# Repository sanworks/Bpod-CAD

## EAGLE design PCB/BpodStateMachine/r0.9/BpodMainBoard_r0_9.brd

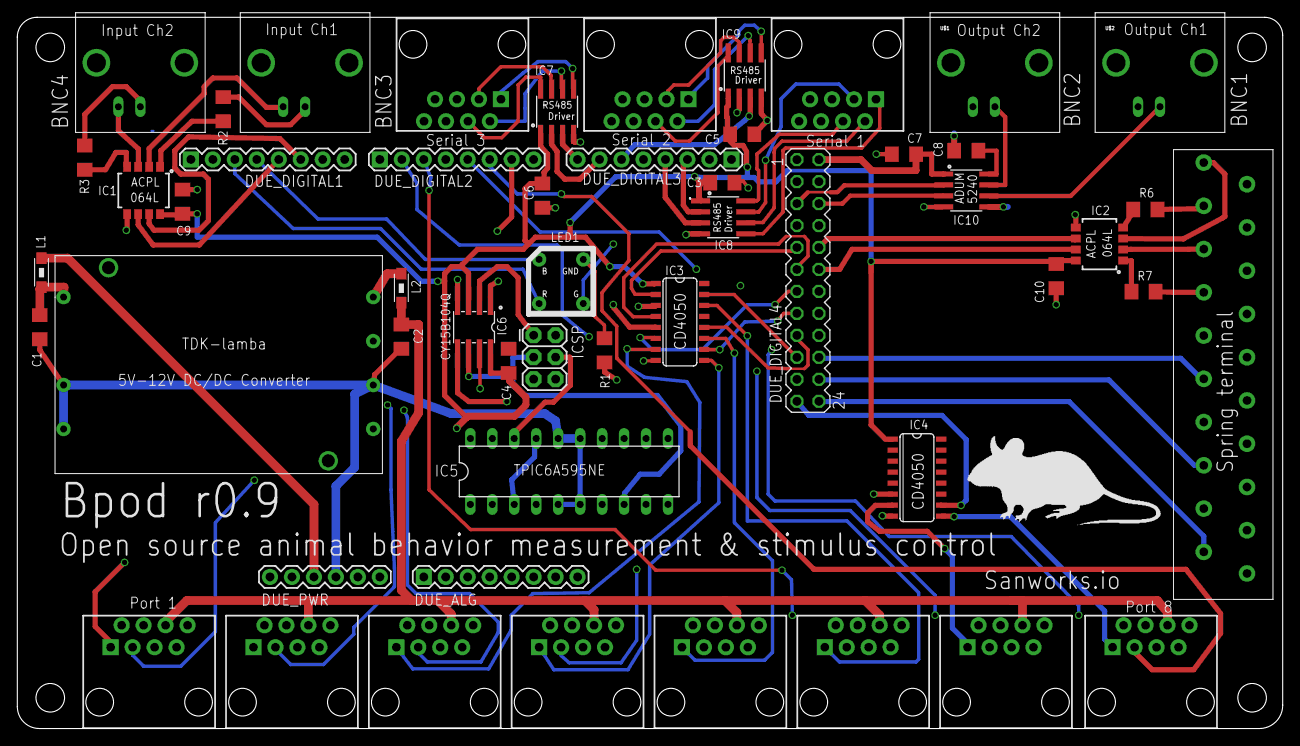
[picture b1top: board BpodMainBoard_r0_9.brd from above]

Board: 4 copper layers, 146.3 x 82.2 mm, 57 parts (0 on the bottom side), 93 nets.

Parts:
C1, C2: 22uf; 1206
C3, C4, C5, C6, C7, C8, C9, C10: 0.1uf; 1206
DUE_ALG: 1X08
DUE_DIGITAL1, DUE_DIGITAL2, DUE_DIGITAL3: 1X08
DUE_DIGITAL4: MA12-2
DUE_PWR: 1X06
IC1, IC2: OPTOISOLATOR-2SOIC8; SO08-2
IC3, IC4: CD4050; SO16
IC5: DIL20
IC6: CY15B104Q-SXI; SO08-UNIVERSAL
IC7, IC8, IC9: SN65HVD31DR; SO08
IC10: ADUM5240; SO08
ICSP: AVR_SPI_PRG_6PTH; 2X3
JP1, JP2, JP3, JP4: STAND-OFF
L1, L2: 1206
PORT1, PORT2, PORT3, PORT4, PORT5, PORT6, PORT7, PORT8: RJ45-8PTH; RJ45-8
R1: 47; 1206
R2, R3, R6, R7: 1k; 1206
SERIAL1, SERIAL2: RJ45-8PTH; RJ45-8
SYNC: RJ45-8PTH; RJ45-8
U$1, U$2, U$3, U$4: BNCPTH; BNC
U$5: TDK_LAMBDA_5V_TO_12V; TDK_LAMBDA_5V_12V
U$6: 10POS_SPRING_TERMINAL; 10POS_SCREW_TERMINAL
U$7: MOUSELOGO
U$8: SQUARE_TRICOLOR_LED

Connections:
5V: DUE_PWR.3, IC5.3, IC5.17, L1.2, PORT1.4, PORT2.4, PORT3.4, PORT4.4, PORT5.4, PORT6.4, PORT7.4, PORT8.4
12V: C2.1, L2.1, PORT1.6, PORT2.6, PORT3.6, PORT4.6, PORT5.6, PORT6.6, PORT7.6, PORT8.6
BNCIN1: DUE_DIGITAL1.6, IC1.7
BNCIN2: DUE_DIGITAL1.5, IC1.6
BNC_OUT1: DUE_DIGITAL4.6, IC10.3
BNC_OUT2: DUE_DIGITAL4.5, IC10.2
FRAM_CS: DUE_DIGITAL2.7, IC6.1
FRAM_HLD: DUE_ALG.4, IC6.7
GND: C3.2, C5.2, C6.2, C7.2, C9.2, C10.1, DUE_PWR.5, IC1.5, IC2.5, IC3.8, IC4.8, IC5.4, IC5.14, IC6.4, IC7.4, IC8.4, IC9.4, IC10.4, PORT1.5, PORT2.5, PORT3.5, PORT4.5, PORT5.5, PORT6.5, PORT7.5, PORT8.5, R1.1, U$6.P$12, U$6.P$14, U$6.P$16
ISOGND: C8.2, IC10.5, U$1.GND, U$2.GND
LED_BLUE: DUE_DIGITAL1.4, U$8.P$3
LED_GREEN: DUE_DIGITAL4.14, U$8.P$1
LED_RED: DUE_DIGITAL1.3, U$8.P$4
MOSI: IC5.18, IC6.5, ICSP.4
unnamed: R3.2, U$4.S
unnamed: R2.2, U$3.S
unnamed: IC1.3, U$4.GND
unnamed: IC1.2, U$3.GND
unnamed: R6.2, U$6.P$19
unnamed: IC10.6, U$2.S
unnamed: IC10.7, U$1.S
unnamed: IC5.19, PORT1.7
unnamed: IC5.20, PORT2.7
unnamed: IC5.1, PORT3.7
unnamed: IC5.2, PORT4.7
unnamed: IC5.9, PORT5.7
unnamed: IC5.10, PORT6.7
unnamed: IC5.11, PORT7.7
unnamed: IC5.12, PORT8.7
unnamed: IC7.8, SYNC.4
unnamed: IC7.7, SYNC.3
unnamed: IC7.6, SYNC.2
unnamed: IC7.5, SYNC.1
unnamed: DUE_DIGITAL3.7, IC7.2
unnamed: IC2.4, R6.1
unnamed: IC2.1, R7.1
unnamed: R1.2, U$8.P$2
unnamed: C8.1, IC10.8
unnamed: DUE_DIGITAL3.8, IC7.3
unnamed: IC8.8, SERIAL1.4
unnamed: IC8.7, SERIAL1.3
unnamed: IC8.6, SERIAL1.2
unnamed: IC8.5, SERIAL1.1
unnamed: IC9.8, SERIAL2.4
unnamed: IC9.7, SERIAL2.3
unnamed: IC9.6, SERIAL2.2
unnamed: IC9.5, SERIAL2.1
unnamed: DUE_DIGITAL3.3, IC8.2
unnamed: IC2.3, U$6.P$20
unnamed: R7.2, U$6.P$17
unnamed: IC2.2, U$6.P$18
unnamed: C1.1, L1.1, U$5.5VIN
unnamed: L2.2, U$5.12VOUT
unnamed: DUE_DIGITAL3.4, IC8.3
unnamed: DUE_DIGITAL3.5, IC9.2
unnamed: DUE_DIGITAL3.6, IC9.3
unnamed: IC1.1, R2.1
unnamed: IC1.4, R3.1
PGND: C1.2, C2.2, DUE_PWR.4, IC5.5, IC5.6, IC5.15, IC5.16, U$5.5VGND, U$5.12VGND, U$5.PWR
PORT1INPUT: IC3.3, PORT1.1
PORT1IN_3V3: DUE_DIGITAL4.9, IC3.2
PORT1LED: DUE_DIGITAL1.7, PORT1.3
PORT2INPUT: IC3.5, PORT2.1
PORT2IN_3V3: DUE_DIGITAL4.11, IC3.4
PORT2LED: DUE_DIGITAL1.8, PORT2.3
PORT3INPUT: IC3.7, PORT3.1
PORT3IN_3V3: DUE_DIGITAL4.13, IC3.6
PORT3LED: DUE_DIGITAL2.1, PORT3.3
PORT4INPUT: IC3.9, PORT4.1
PORT4IN_3V3: DUE_DIGITAL4.15, IC3.10
PORT4LED: DUE_DIGITAL2.2, PORT4.3
PORT5INPUT: IC3.11, PORT5.1
PORT5IN_3V3: DUE_DIGITAL4.17, IC3.12
PORT5LED: DUE_DIGITAL2.3, PORT5.3
PORT6INPUT: IC3.14, PORT6.1
PORT6IN_3V3: DUE_DIGITAL4.19, IC3.15
PORT6LED: DUE_DIGITAL2.4, PORT6.3
PORT7INPUT: IC4.7, PORT7.1
PORT7IN_3V3: DUE_DIGITAL4.21, IC4.6
PORT7LED: DUE_DIGITAL2.5, PORT7.3
PORT8INPUT: IC4.9, PORT8.1
PORT8IN_3V3: DUE_DIGITAL4.23, IC4.10
PORT8LED: DUE_DIGITAL2.6, PORT8.3
RCK: DUE_DIGITAL4.3, IC5.7
SPI_CLK: IC5.8, IC6.6, ICSP.3
SPI_MISO: IC6.2, ICSP.1
UPPER_5V: C7.1, DUE_DIGITAL4.2, IC10.1
VCC: C3.1, C4.2, C5.1, C6.1, C9.1, C10.2, DUE_PWR.2, IC1.8, IC2.8, IC3.1, IC4.1, IC6.3, IC6.8, IC7.1, IC8.1, IC9.1
WIREOUT3: DUE_DIGITAL4.20, U$6.P$15
WIRE_INPUT1: DUE_DIGITAL4.12, IC2.7
WIRE_INPUT2: DUE_DIGITAL4.10, IC2.6
WIRE_OUT1: DUE_DIGITAL4.24, U$6.P$11
WIRE_OUT2: DUE_DIGITAL4.22, U$6.P$13

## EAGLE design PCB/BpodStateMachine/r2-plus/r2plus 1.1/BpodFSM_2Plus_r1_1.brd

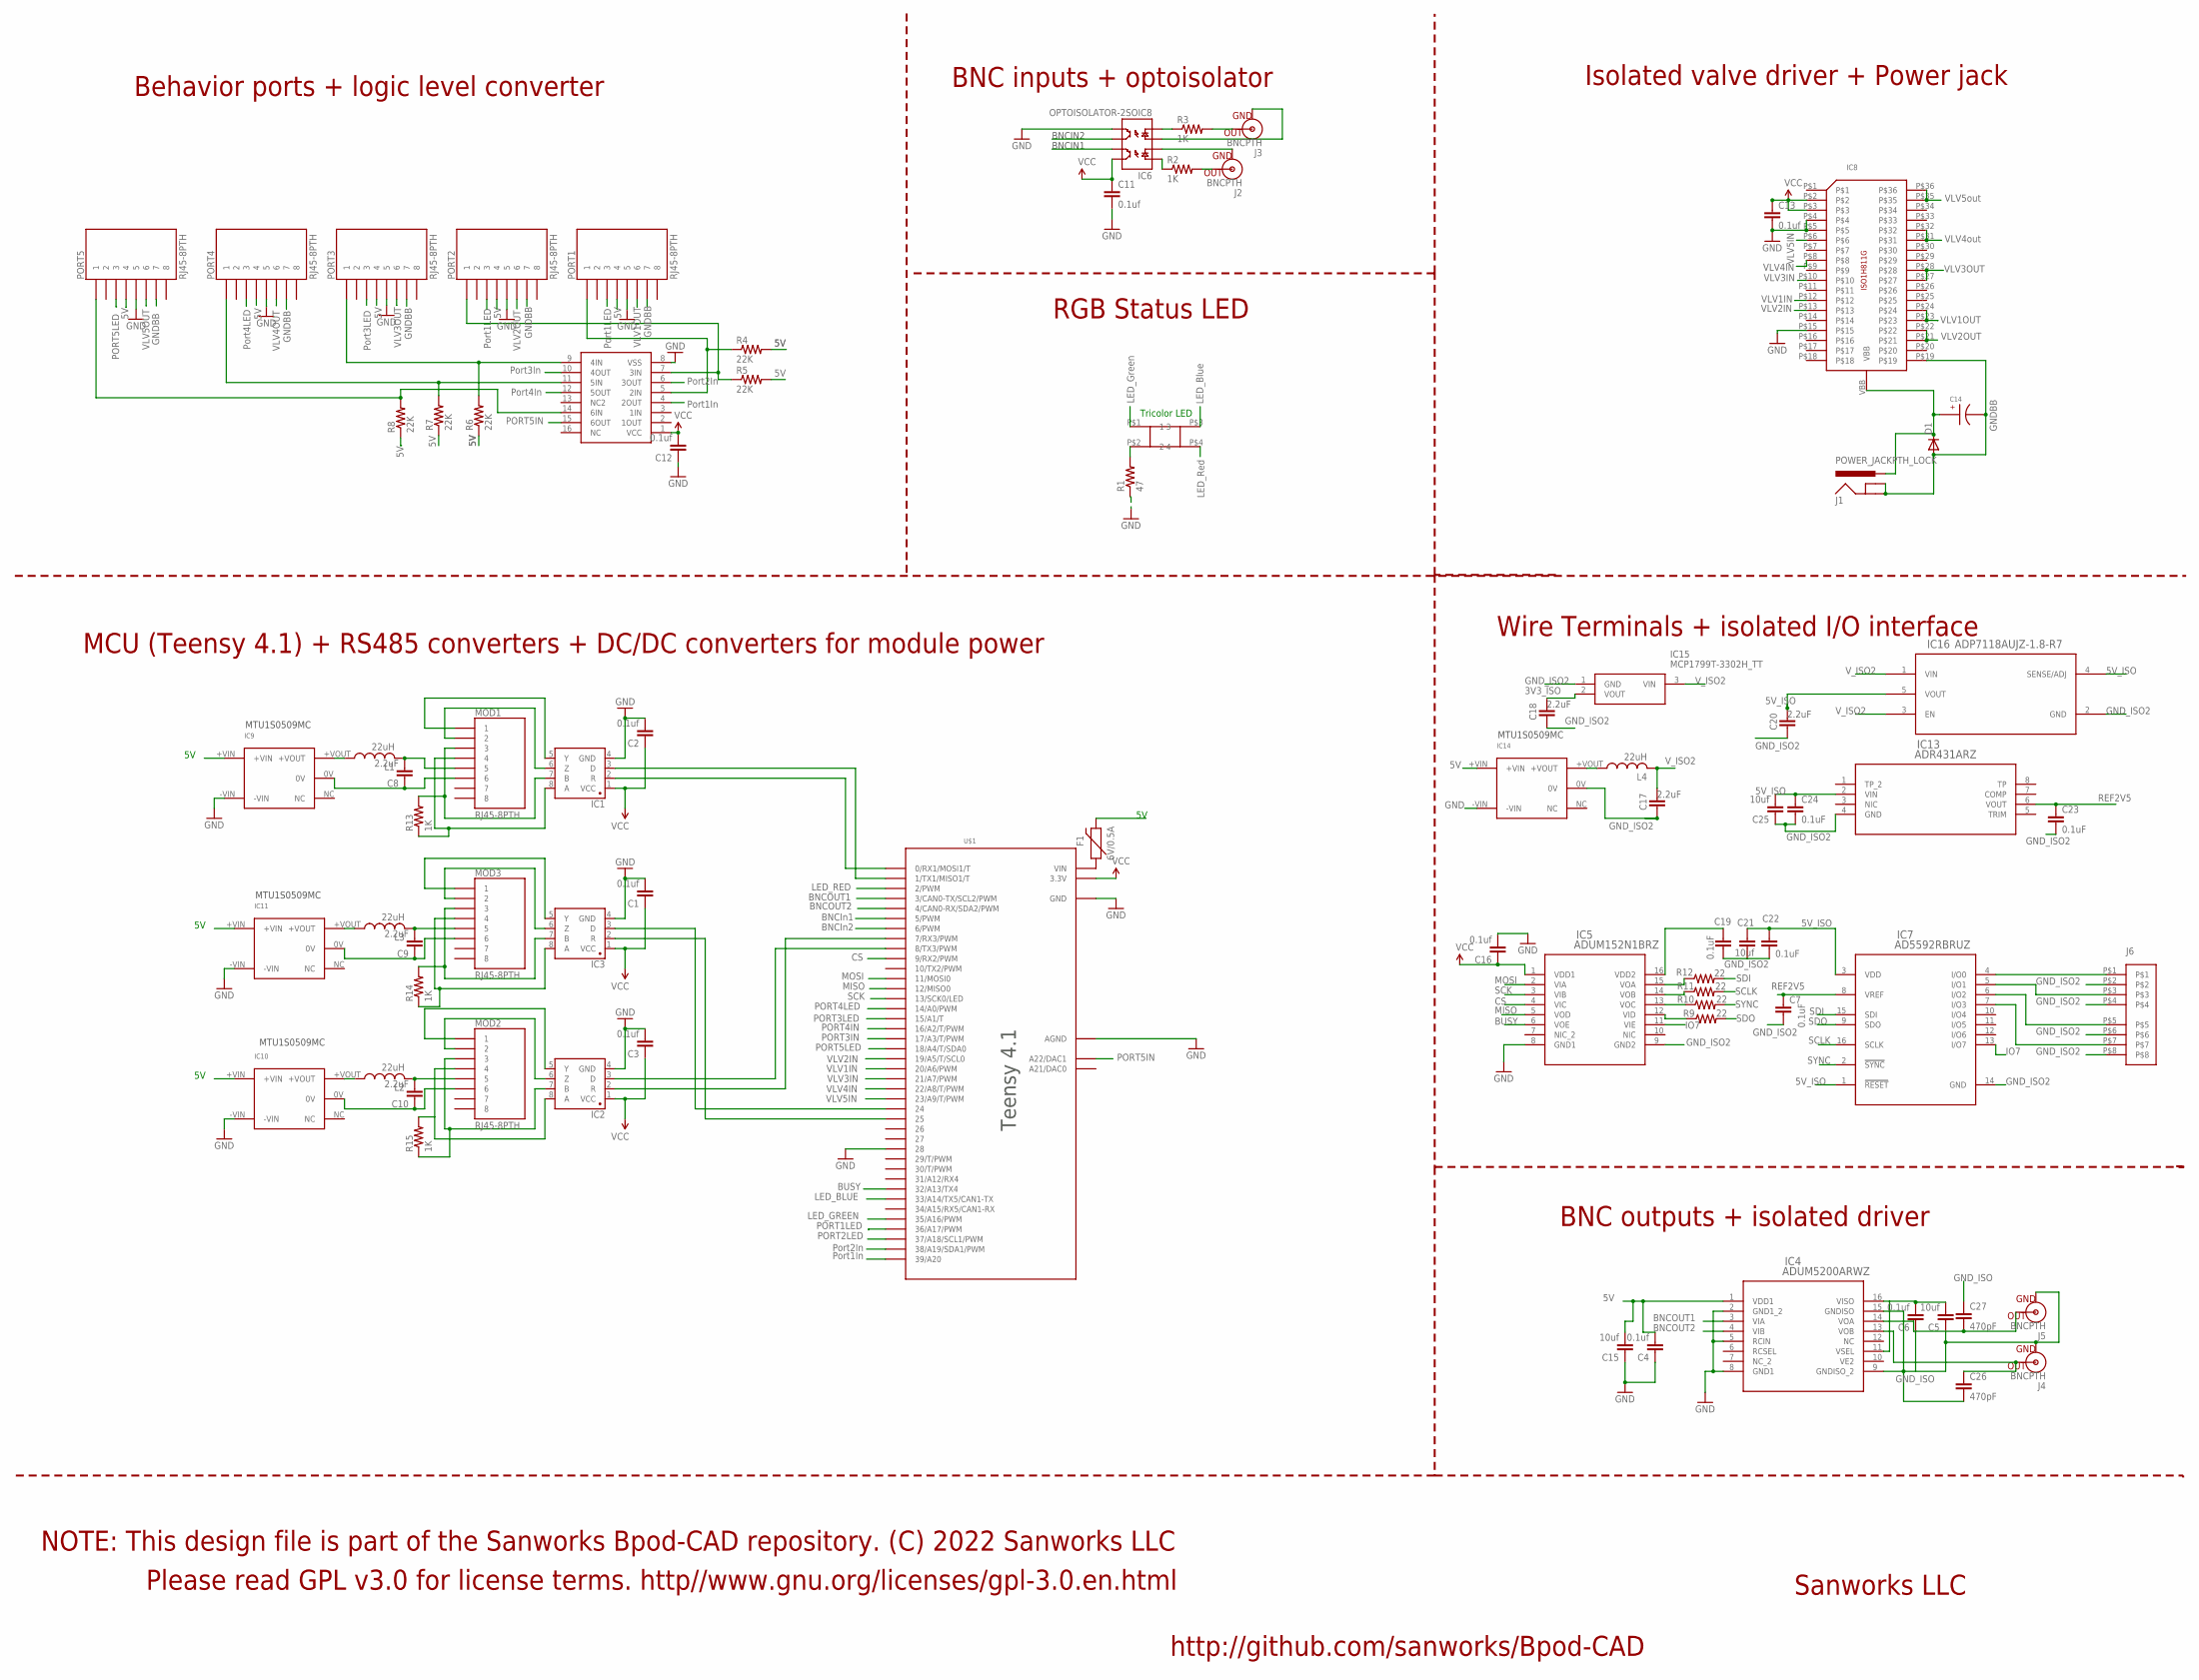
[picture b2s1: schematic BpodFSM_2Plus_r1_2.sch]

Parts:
C1, C2, C3, C4, C6, C11, C12, C13, C16: 0.1uf; 0805
C5, C15, C21, C25: 10uf; 1206@1
C7, C19, C22, C23, C24: 0.1uF; 0805
C8, C9, C10, C17, C18, C20: 2.2uF; 0805
C14: EEE-FK1H100UR
C26, C27: 470pF; 0805
D1: DIODE-DO214AA; DO214AA
F1: 6V/0.5A; 1206
IC1, IC2, IC3: SN65HVD31DR; SO08
IC4: ADUM5200ARWZ; RW_16
IC5: ADUM152N1BRZ; R-16_ADI
IC6: OPTOISOLATOR-2SOIC8; SO08-2
IC7: AD5592RBRUZ; RU_16_ADI
IC8: ISO1H811G
IC9, IC10, IC11: 9V; MTU1D0505MC
IC12: CD4050; SO16
IC13: ADR431ARZ; R_8_ADI
IC14: 5V; MTU1D0505MC
IC15: MCP1799T-3302H_TT; SOT95P237X112-3N
IC16: ADP7118AUJZ-1.8-R7; UJ_5
J1: POWER_JACKPTH_LOCK; POWER_JACK_PTH_LOCK
J2, J3, J4, J5: BNCPTH; BNC
J6: 8POS_MOLEX_SOCKET
L1, L2, L3, L4: 22uH; L3225M
MOD1, MOD2, MOD3: RJ45-8PTH; RJ45-8
PORT1, PORT2, PORT3, PORT4, PORT5: RJ45-8PTH; RJ45-8
R1: 47; 1206
R2, R3, R13, R14, R15: 1K; 1206
R4, R5, R6, R7, R8: 22K; 1206
R9, R10, R11, R12: 22; R0805
U$1: TEENSY_3.6_DIL
U$8: SQUARE_TRICOLOR_LED

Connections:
5V: C4.2, C15.2, F1.2, IC4.1 (VDD1), IC9.+VIN, IC10.+VIN, IC11.+VIN, IC14.+VIN, PORT1.4, PORT2.4, PORT3.4, PORT4.4, PORT5.4, R4.2, R5.2, R6.1, R7.1, R8.1
BNCIN1: IC6.7 (EM1), U$1.6 (6/PWM)
BNCIN2: IC6.6 (CL2), U$1.5 (5/PWM)
BNCOUT1: IC4.3 (VIA), U$1.3 (3/CAN0-TX/SCL2/PWM)
BNCOUT2: IC4.4 (VIB), U$1.4 (4/CAN0-RX/SDA2/PWM)
BUSY: IC5.6 (VOE), U$1.32/A13 (32/A13/TX4)
CS: IC5.4 (VIC), U$1.9 (9/RX2/PWM)
GND: C1.2, C2.2, C3.2, C4.1, C11.2, C12.1, C13.2, C15.1, C16.2, IC1.4 (GND), IC2.4 (GND), IC3.4 (GND), IC4.2 (GND1_2), IC4.5 (RCIN), IC4.8 (GND1), IC5.8 (GND1), IC6.5 (EM2), IC8.P$4, IC8.P$5, IC8.P$15, IC9.-VIN, IC10.-VIN, IC11.-VIN, IC12.8 (VSS), IC14.-VIN, PORT1.5, PORT2.5, PORT3.5, PORT4.5, PORT5.5, R1.1, U$1.28, U$1.AGND, U$1.GND, U$1.GND1 (GND); also elsewhere on the board
GNDBB: C14.CATHODE, D1.A, IC8.P$19, J1.GND, J1.GNDBREAK, PORT1.7, PORT2.7, PORT3.7, PORT4.7, PORT5.7
GND_ISO: C5.1, C6.1, C26.2, C27.1, IC4.9 (GNDISO_2), IC4.15 (GNDISO), J4.GND, J5.GND
IO7: IC5.11 (VIE), IC7.13 (I/O7)
LED_BLUE: U$1.33/A14 (33/A14/TX5/CAN1-TX), U$8.P$3 (3)
LED_GREEN: U$1.35/A16 (35/A16/PWM), U$8.P$1 (1)
LED_RED: U$1.2 (2/PWM), U$8.P$4 (4)
MISO: IC5.5 (VOD), U$1.12 (12/MISO0)
MOSI: IC5.2 (VIA), U$1.11 (11/MOSI0)
unnamed: IC3.8 (A), MOD3.4, R14.1
unnamed: IC3.7 (B), MOD3.3, R14.2
unnamed: IC3.6 (Z), MOD3.2
unnamed: IC3.5 (Y), MOD3.1
unnamed: IC3.2 (R), U$1.25
unnamed: IC3.3 (D), U$1.24
unnamed: IC1.8 (A), MOD1.4, R13.1
unnamed: IC1.7 (B), MOD1.3, R13.2
unnamed: IC1.6 (Z), MOD1.2
unnamed: IC1.5 (Y), MOD1.1
unnamed: IC1.2 (R), U$1.0 (0/RX1/MOSI1/T)
unnamed: IC1.3 (D), U$1.1 (1/TX1/MISO1/T)
unnamed: IC6.3 (A2), J3.GND
unnamed: J3.S (OUT), R3.2
unnamed: J2.S (OUT), R2.2
unnamed: IC6.2 (C1), J2.GND
unnamed: IC2.8 (A), MOD2.4, R15.2
unnamed: IC2.7 (B), MOD2.3, R15.1
unnamed: IC2.6 (Z), MOD2.2
unnamed: IC12.7 (3IN), PORT2.1, R5.1
unnamed: IC2.5 (Y), MOD2.1
unnamed: IC2.2 (R), U$1.7 (7/RX3/PWM)
unnamed: C8.2, L1.2, MOD1.5
unnamed: IC12.9 (4IN), PORT3.1, R6.2
unnamed: R1.2, U$8.P$2 (2)
unnamed: C8.1, IC9.0V, MOD1.6
unnamed: C5.2, C6.2, IC4.11 (VSEL), IC4.16 (VISO)
unnamed: IC2.3 (D), U$1.8 (8/TX3/PWM)
unnamed: F1.1, U$1.VIN
unnamed: IC7.4 (I/O0), J6.P$1
unnamed: IC12.11 (5IN), PORT4.1, R7.2
unnamed: C27.2, IC4.14 (VOA), J5.S (OUT)
unnamed: C26.1, IC4.13 (VOB), J4.S (OUT)
unnamed: IC7.5 (I/O1), J6.P$3
unnamed: IC7.6 (I/O2), J6.P$5
unnamed: IC7.7 (I/O3), J6.P$7
unnamed: IC14.+VOUT, L4.1
unnamed: IC5.15 (VOA), R12.1
unnamed: IC9.+VOUT, L1.1
unnamed: IC5.14 (VOB), R11.1
unnamed: IC12.14 (6IN), PORT5.1, R8.2
unnamed: IC5.13 (VOC), R10.1
unnamed: C10.1, IC10.0V, MOD2.6
unnamed: C10.2, L2.2, MOD2.5
unnamed: IC10.+VOUT, L2.1
unnamed: IC5.12 (VID), R9.1
unnamed: C9.1, IC11.0V, MOD3.6
unnamed: C9.2, L3.2, MOD3.5
unnamed: IC11.+VOUT, L3.1
unnamed: IC6.1 (A1), R2.1
unnamed: IC6.4 (C2), R3.1
unnamed: IC12.5 (2IN), PORT1.1, R4.1
PORT1IN: IC12.4 (2OUT), U$1.39/A20
PORT1LED: PORT1.3, U$1.36/A17 (36/A17/PWM)
PORT2IN: IC12.6 (3OUT), U$1.38/A19 (38/A19/SDA1/PWM)
PORT2LED: PORT2.3, U$1.37/A18 (37/A18/SCL1/PWM)
PORT3IN: IC12.10 (4OUT), U$1.17/A3 (17/A3/T/PWM)
PORT3LED: PORT3.3, U$1.15/A1 (15/A1/T)
PORT4IN: IC12.12 (5OUT), U$1.16/A2 (16/A2/T/PWM)
PORT4LED: PORT4.3, U$1.14/A0 (14/A0/PWM)
PORT5IN: IC12.15 (6OUT), U$1.A22 (A22/DAC1)
PORT5LED: PORT5.3, U$1.18/A4 (18/A4/T/SDA0)
REF2V5: C7.1, C23.1, IC7.8 (VREF), IC13.6 (VOUT)
SCK: IC5.3 (VIB), U$1.13 (13/SCK0/LED)
SCLK: IC7.16 (SCLK), R11.2
SDI: IC7.15 (SDI), R12.2
SDO: IC7.9 (SDO), R9.2
SYNC: IC7.2 (!SYNC), R10.2
VBB: C14.ANODE, D1.C, IC8.VBB, J1.PWR
VCC: C1.1, C2.1, C3.1, C11.1, C12.2, C13.1, C16.1, IC1.1 (VCC), IC2.1 (VCC), IC3.1 (VCC), IC5.1 (VDD1), IC6.8 (CL1), IC8.P$2, IC8.P$3, IC12.1 (VCC), U$1.3.3V, U$1.3.3V3 (3.3V)
VLV1IN: IC8.P$12, U$1.20/A6 (20/A6/PWM)
VLV1OUT: IC8.P$23, IC8.P$24, PORT1.6
VLV2IN: IC8.P$13, U$1.19/A5 (19/A5/T/SCL0)
VLV2OUT: IC8.P$21, IC8.P$22, PORT2.6
VLV3IN: IC8.P$10, U$1.21/A7 (21/A7/PWM)
VLV3OUT: IC8.P$27, IC8.P$28, PORT3.6
VLV4IN: IC8.P$8, U$1.22/A8 (22/A8/T/PWM)
VLV4OUT: IC8.P$31, IC8.P$32, PORT4.6
VLV5IN: IC8.P$6, U$1.23/A9 (23/A9/T/PWM)
VLV5OUT: IC8.P$35, IC8.P$36, PORT5.6

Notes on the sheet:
Tricolor LED
LED_Blue
LED_Red
LED_Green
BNCIN1
BNCIN2
BNCIn1
BNCIn2
Port1In
Port2In
Port3In
Port4In
Port1LED
Port3LED
Port4LED
GNDBB
VLV5out
VLV4out
Sanworks LLC
http://github.com/sanworks/Bpod-CAD
Please read GPL v3.0 for license terms. http//www.gnu.org/licenses/gpl-3.0.en.html
NOTE: This design file is part of the Sanworks Bpod-CAD repository. (C) 2022 Sanworks LLC
Behavior ports + logic level converter
BNC inputs + optoisolator
Isolated valve driver + Power jack
RGB Status LED
BNC outputs + isolated driver
MCU (Teensy 4.1) + RS485 converters + DC/DC converters for module power
Wire Terminals + isolated I/O interface
MTU1S0509MC
Teensy 4.1

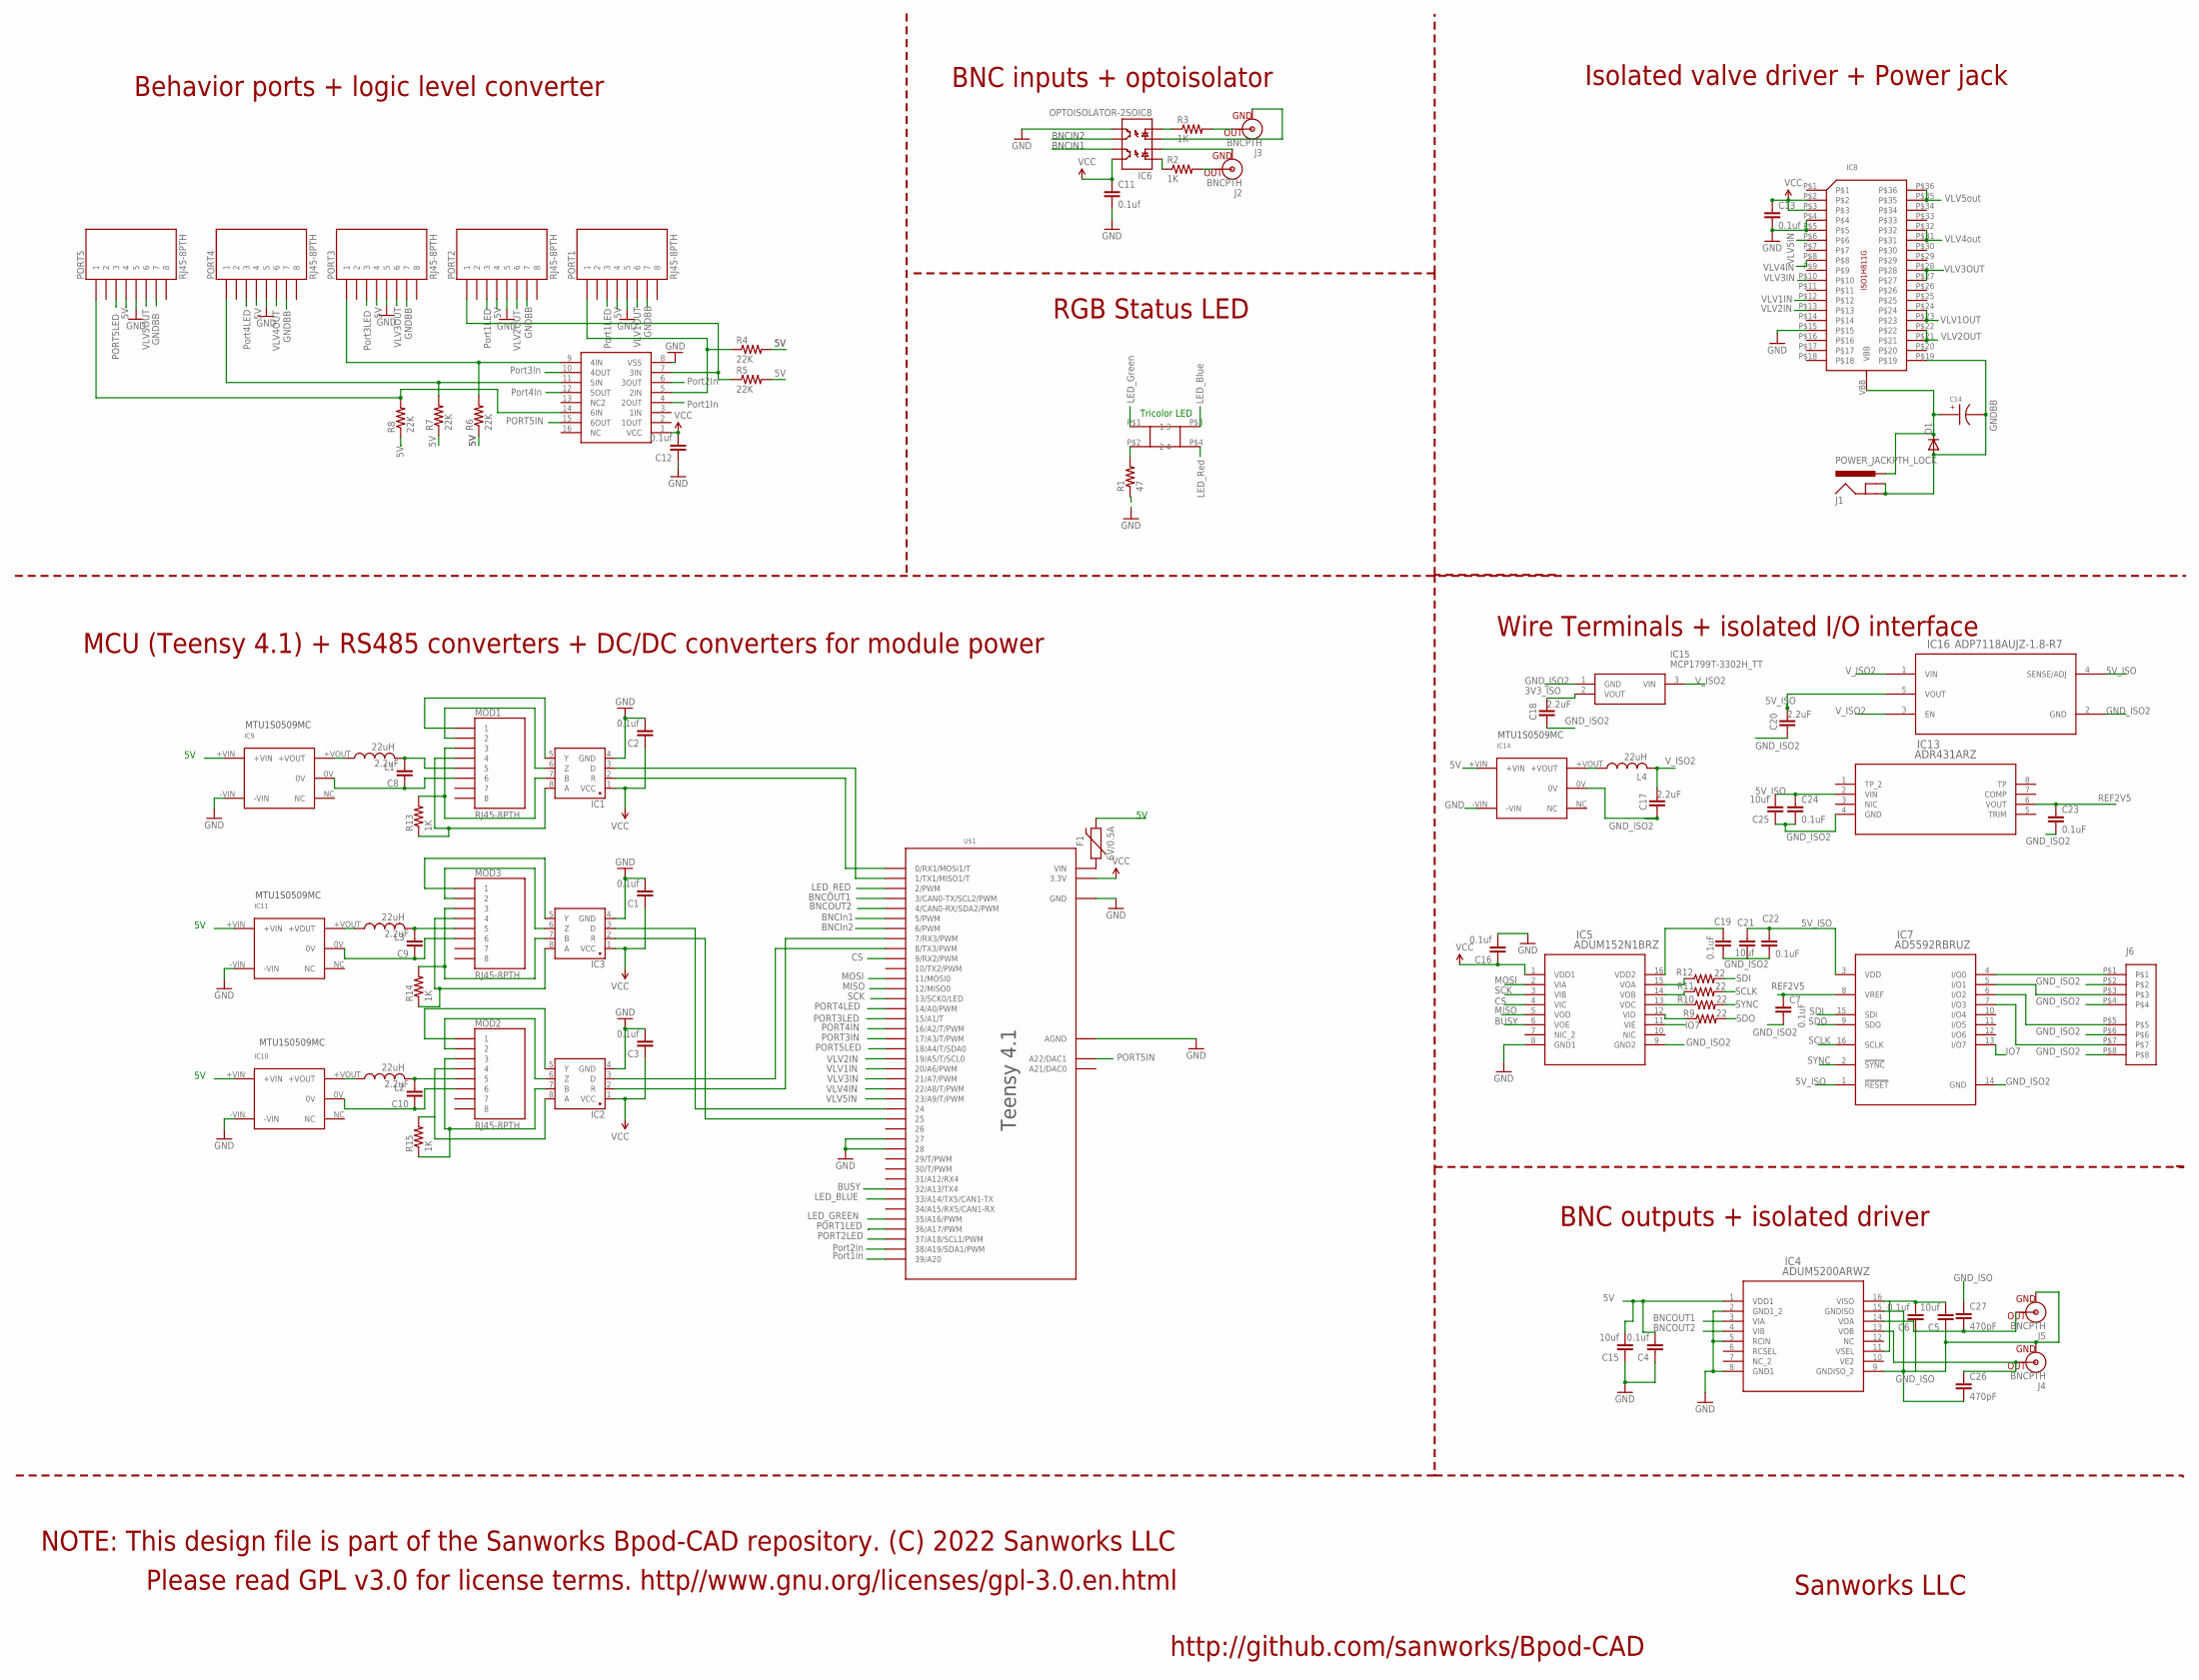
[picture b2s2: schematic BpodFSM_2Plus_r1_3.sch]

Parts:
C1, C2, C3, C4, C6, C11, C12, C13, C16: 0.1uf; 0805
C5, C15, C21, C25: 10uf; 1206@1
C7, C19, C22, C23, C24: 0.1uF; 0805
C8, C9, C10, C17, C18, C20: 2.2uF; 0805
C14: EEE-FK1H100UR
C26, C27: 470pF; 0805
D1: DIODE-DO214AA; DO214AA
F1: 6V/0.5A; 1206
IC1, IC2, IC3: SN65HVD31DR; SO08
IC4: ADUM5200ARWZ; RW_16
IC5: ADUM152N1BRZ; R-16_ADI
IC6: OPTOISOLATOR-2SOIC8; SO08-2
IC7: AD5592RBRUZ; RU_16_ADI
IC8: ISO1H811G
IC9, IC10, IC11: 9V; MTU1D0505MC
IC12: CD4050; SO16
IC13: ADR431ARZ; R_8_ADI
IC14: 5V; MTU1D0505MC
IC15: MCP1799T-3302H_TT; SOT95P237X112-3N
IC16: ADP7118AUJZ-1.8-R7; UJ_5
J1: POWER_JACKPTH_LOCK; POWER_JACK_PTH_LOCK
J2, J3, J4, J5: BNCPTH; BNC
J6: 8POS_MOLEX_SOCKET
L1, L2, L3, L4: 22uH; L3225M
MOD1, MOD2, MOD3: RJ45-8PTH; RJ45-8
PORT1, PORT2, PORT3, PORT4, PORT5: RJ45-8PTH; RJ45-8
R1: 47; 1206
R2, R3, R13, R14, R15: 1K; 1206
R4, R5, R6, R7, R8: 22K; 1206
R9, R10, R11, R12: 22; R0805
U$1: TEENSY_3.6_DIL
U$8: SQUARE_TRICOLOR_LED

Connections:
5V: C4.2, C15.2, F1.2, IC4.1 (VDD1), IC9.+VIN, IC10.+VIN, IC11.+VIN, IC14.+VIN, PORT1.4, PORT2.4, PORT3.4, PORT4.4, PORT5.4, R4.2, R5.2, R6.1, R7.1, R8.1
BNCIN1: IC6.7 (EM1), U$1.6 (6/PWM)
BNCIN2: IC6.6 (CL2), U$1.5 (5/PWM)
BNCOUT1: IC4.3 (VIA), U$1.3 (3/CAN0-TX/SCL2/PWM)
BNCOUT2: IC4.4 (VIB), U$1.4 (4/CAN0-RX/SDA2/PWM)
BUSY: IC5.6 (VOE), U$1.32/A13 (32/A13/TX4)
CS: IC5.4 (VIC), U$1.9 (9/RX2/PWM)
GND: C1.2, C2.2, C3.2, C4.1, C11.2, C12.1, C13.2, C15.1, C16.2, IC1.4 (GND), IC2.4 (GND), IC3.4 (GND), IC4.2 (GND1_2), IC4.5 (RCIN), IC4.8 (GND1), IC5.8 (GND1), IC6.5 (EM2), IC8.P$4, IC8.P$5, IC8.P$15, IC9.-VIN, IC10.-VIN, IC11.-VIN, IC12.8 (VSS), IC14.-VIN, PORT1.5, PORT2.5, PORT3.5, PORT4.5, PORT5.5, R1.1, U$1.27, U$1.28, U$1.AGND, U$1.GND, U$1.GND1 (GND)
GNDBB: C14.CATHODE, D1.A, IC8.P$19, J1.GND, J1.GNDBREAK, PORT1.7, PORT2.7, PORT3.7, PORT4.7, PORT5.7
GND_ISO: C5.1, C6.1, C26.2, C27.1, IC4.9 (GNDISO_2), IC4.15 (GNDISO), J4.GND, J5.GND
IO7: IC5.11 (VIE), IC7.13 (I/O7)
LED_BLUE: U$1.33/A14 (33/A14/TX5/CAN1-TX), U$8.P$3 (3)
LED_GREEN: U$1.35/A16 (35/A16/PWM), U$8.P$1 (1)
LED_RED: U$1.2 (2/PWM), U$8.P$4 (4)
MISO: IC5.5 (VOD), U$1.12 (12/MISO0)
MOSI: IC5.2 (VIA), U$1.11 (11/MOSI0)
unnamed: IC3.8 (A), MOD3.4, R14.1
unnamed: IC3.7 (B), MOD3.3, R14.2
unnamed: IC3.6 (Z), MOD3.2
unnamed: IC3.5 (Y), MOD3.1
unnamed: IC3.2 (R), U$1.25
unnamed: IC3.3 (D), U$1.24
unnamed: IC1.8 (A), MOD1.4, R13.1
unnamed: IC1.7 (B), MOD1.3, R13.2
unnamed: IC1.6 (Z), MOD1.2
unnamed: IC1.5 (Y), MOD1.1
unnamed: IC1.2 (R), U$1.0 (0/RX1/MOSI1/T)
unnamed: IC1.3 (D), U$1.1 (1/TX1/MISO1/T)
unnamed: IC6.3 (A2), J3.GND
unnamed: J3.S (OUT), R3.2
unnamed: J2.S (OUT), R2.2
unnamed: IC6.2 (C1), J2.GND
unnamed: IC2.8 (A), MOD2.4, R15.2
unnamed: IC2.7 (B), MOD2.3, R15.1
unnamed: IC2.6 (Z), MOD2.2
unnamed: IC12.7 (3IN), PORT2.1, R5.1
unnamed: IC2.5 (Y), MOD2.1
unnamed: IC2.2 (R), U$1.7 (7/RX3/PWM)
unnamed: C8.2, L1.2, MOD1.5
unnamed: IC12.9 (4IN), PORT3.1, R6.2
unnamed: R1.2, U$8.P$2 (2)
unnamed: C8.1, IC9.0V, MOD1.6
unnamed: C5.2, C6.2, IC4.11 (VSEL), IC4.16 (VISO)
unnamed: IC2.3 (D), U$1.8 (8/TX3/PWM)
unnamed: F1.1, U$1.VIN
unnamed: IC7.4 (I/O0), J6.P$1
unnamed: IC12.11 (5IN), PORT4.1, R7.2
unnamed: C27.2, IC4.14 (VOA), J5.S (OUT)
unnamed: C26.1, IC4.13 (VOB), J4.S (OUT)
unnamed: IC7.5 (I/O1), J6.P$3
unnamed: IC7.6 (I/O2), J6.P$5
unnamed: IC7.7 (I/O3), J6.P$7
unnamed: IC14.+VOUT, L4.1
unnamed: IC5.15 (VOA), R12.1
unnamed: IC9.+VOUT, L1.1
unnamed: IC5.14 (VOB), R11.1
unnamed: IC12.14 (6IN), PORT5.1, R8.2
unnamed: IC5.13 (VOC), R10.1
unnamed: C10.1, IC10.0V, MOD2.6
unnamed: C10.2, L2.2, MOD2.5
unnamed: IC10.+VOUT, L2.1
unnamed: IC5.12 (VID), R9.1
unnamed: C9.1, IC11.0V, MOD3.6
unnamed: C9.2, L3.2, MOD3.5
unnamed: IC11.+VOUT, L3.1
unnamed: IC6.1 (A1), R2.1
unnamed: IC6.4 (C2), R3.1
unnamed: IC12.5 (2IN), PORT1.1, R4.1
PORT1IN: IC12.4 (2OUT), U$1.39/A20
PORT1LED: PORT1.3, U$1.36/A17 (36/A17/PWM)
PORT2IN: IC12.6 (3OUT), U$1.38/A19 (38/A19/SDA1/PWM)
PORT2LED: PORT2.3, U$1.37/A18 (37/A18/SCL1/PWM)
PORT3IN: IC12.10 (4OUT), U$1.17/A3 (17/A3/T/PWM)
PORT3LED: PORT3.3, U$1.15/A1 (15/A1/T)
PORT4IN: IC12.12 (5OUT), U$1.16/A2 (16/A2/T/PWM)
PORT4LED: PORT4.3, U$1.14/A0 (14/A0/PWM)
PORT5IN: IC12.15 (6OUT), U$1.A22 (A22/DAC1)
PORT5LED: PORT5.3, U$1.18/A4 (18/A4/T/SDA0)
REF2V5: C7.1, C23.1, IC7.8 (VREF), IC13.6 (VOUT)
SCK: IC5.3 (VIB), U$1.13 (13/SCK0/LED)
SCLK: IC7.16 (SCLK), R11.2
SDI: IC7.15 (SDI), R12.2
SDO: IC7.9 (SDO), R9.2
SYNC: IC7.2 (!SYNC), R10.2
VBB: C14.ANODE, D1.C, IC8.VBB, J1.PWR
VCC: C1.1, C2.1, C3.1, C11.1, C12.2, C13.1, C16.1, IC1.1 (VCC), IC2.1 (VCC), IC3.1 (VCC), IC5.1 (VDD1), IC6.8 (CL1), IC8.P$2, IC8.P$3, IC12.1 (VCC), U$1.3.3V, U$1.3.3V3 (3.3V)
VLV1IN: IC8.P$12, U$1.20/A6 (20/A6/PWM)
VLV1OUT: IC8.P$23, IC8.P$24, PORT1.6
VLV2IN: IC8.P$13, U$1.19/A5 (19/A5/T/SCL0)
VLV2OUT: IC8.P$21, IC8.P$22, PORT2.6
VLV3IN: IC8.P$10, U$1.21/A7 (21/A7/PWM)
VLV3OUT: IC8.P$27, IC8.P$28, PORT3.6
VLV4IN: IC8.P$8, U$1.22/A8 (22/A8/T/PWM)
VLV4OUT: IC8.P$31, IC8.P$32, PORT4.6
VLV5IN: IC8.P$6, U$1.23/A9 (23/A9/T/PWM)
VLV5OUT: IC8.P$35, IC8.P$36, PORT5.6

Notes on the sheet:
Tricolor LED
LED_Blue
LED_Red
LED_Green
BNCIN1
BNCIN2
BNCIn1
BNCIn2
Port1In
Port2In
Port3In
Port4In
Port1LED
Port3LED
Port4LED
GNDBB
VLV5out
VLV4out
Sanworks LLC
http://github.com/sanworks/Bpod-CAD
Please read GPL v3.0 for license terms. http//www.gnu.org/licenses/gpl-3.0.en.html
NOTE: This design file is part of the Sanworks Bpod-CAD repository. (C) 2022 Sanworks LLC
Behavior ports + logic level converter
BNC inputs + optoisolator
Isolated valve driver + Power jack
RGB Status LED
BNC outputs + isolated driver
MCU (Teensy 4.1) + RS485 converters + DC/DC converters for module power
Wire Terminals + isolated I/O interface
MTU1S0509MC
Teensy 4.1

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
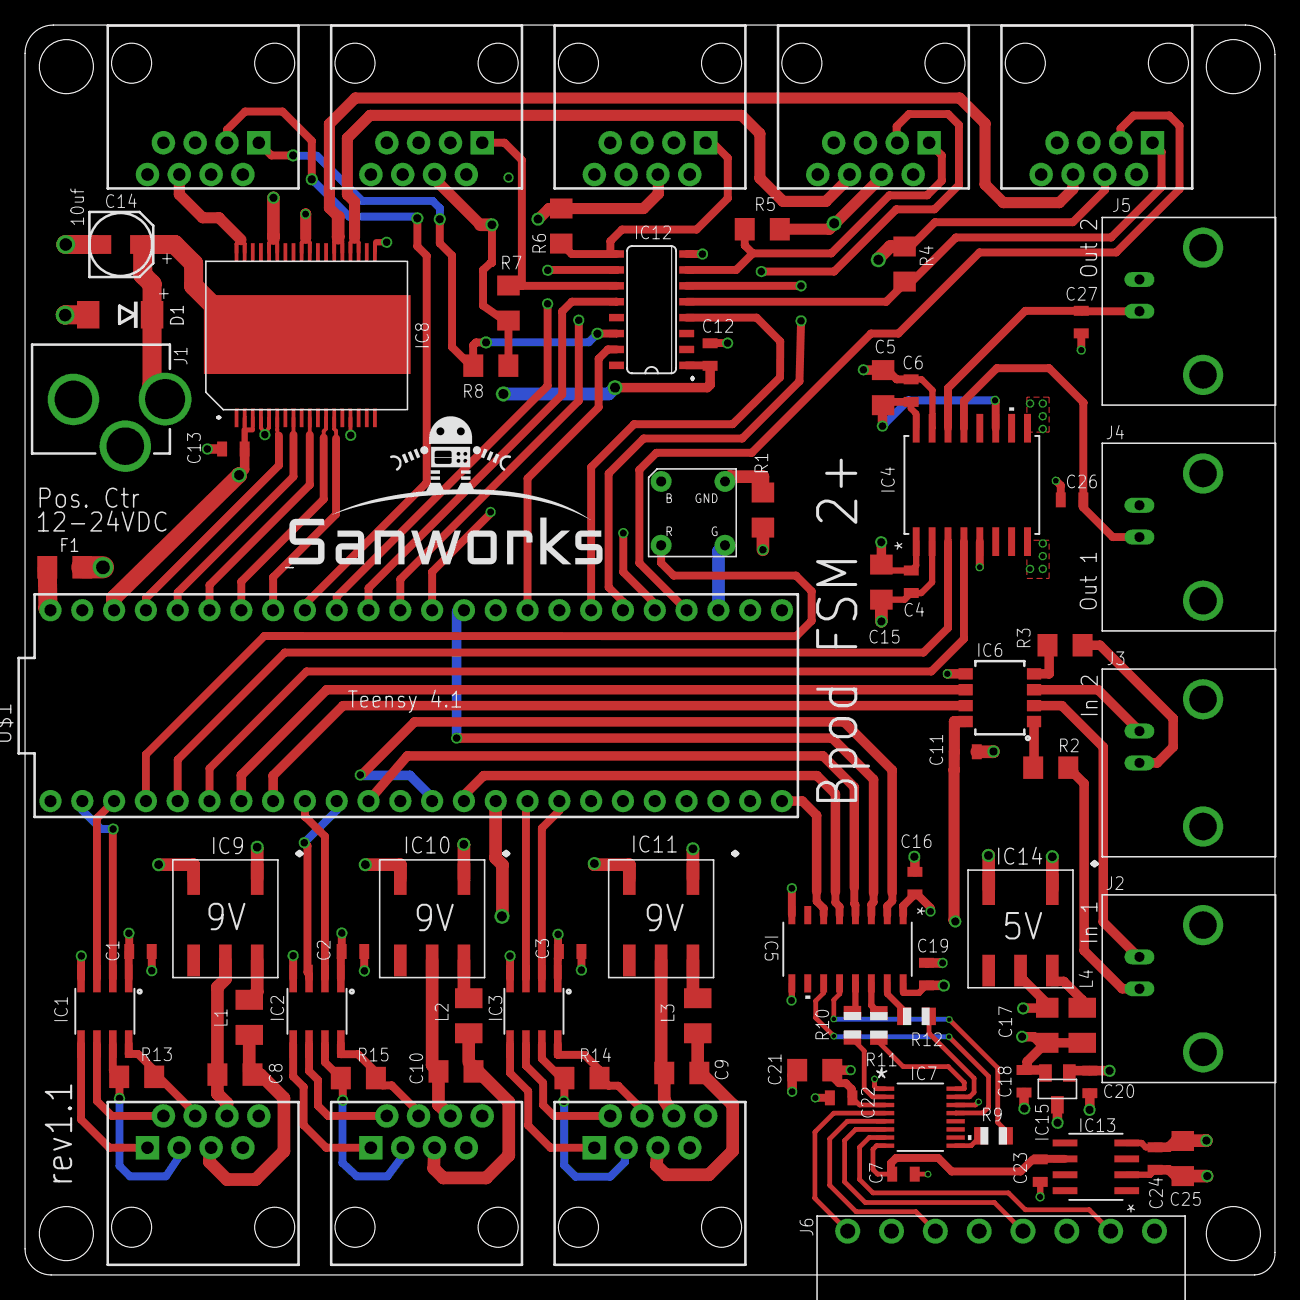
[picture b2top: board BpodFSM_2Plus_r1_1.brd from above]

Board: 4 copper layers, 99.8 x 99.8 mm, 80 parts (0 on the bottom side), 99 nets.

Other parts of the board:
U$7: SANWORKS_LOGO

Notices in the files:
parts and their libraries:
SparkFun-Passives: Licensing: CC v3.0 Share-Alike You are welcome to use this library for commercial purposes.
SparkFun-DiscreteSemi: Licensing: Creative Commons ShareAlike 4.0 International - https://creativecommons.org/licenses/by-sa/4.0
